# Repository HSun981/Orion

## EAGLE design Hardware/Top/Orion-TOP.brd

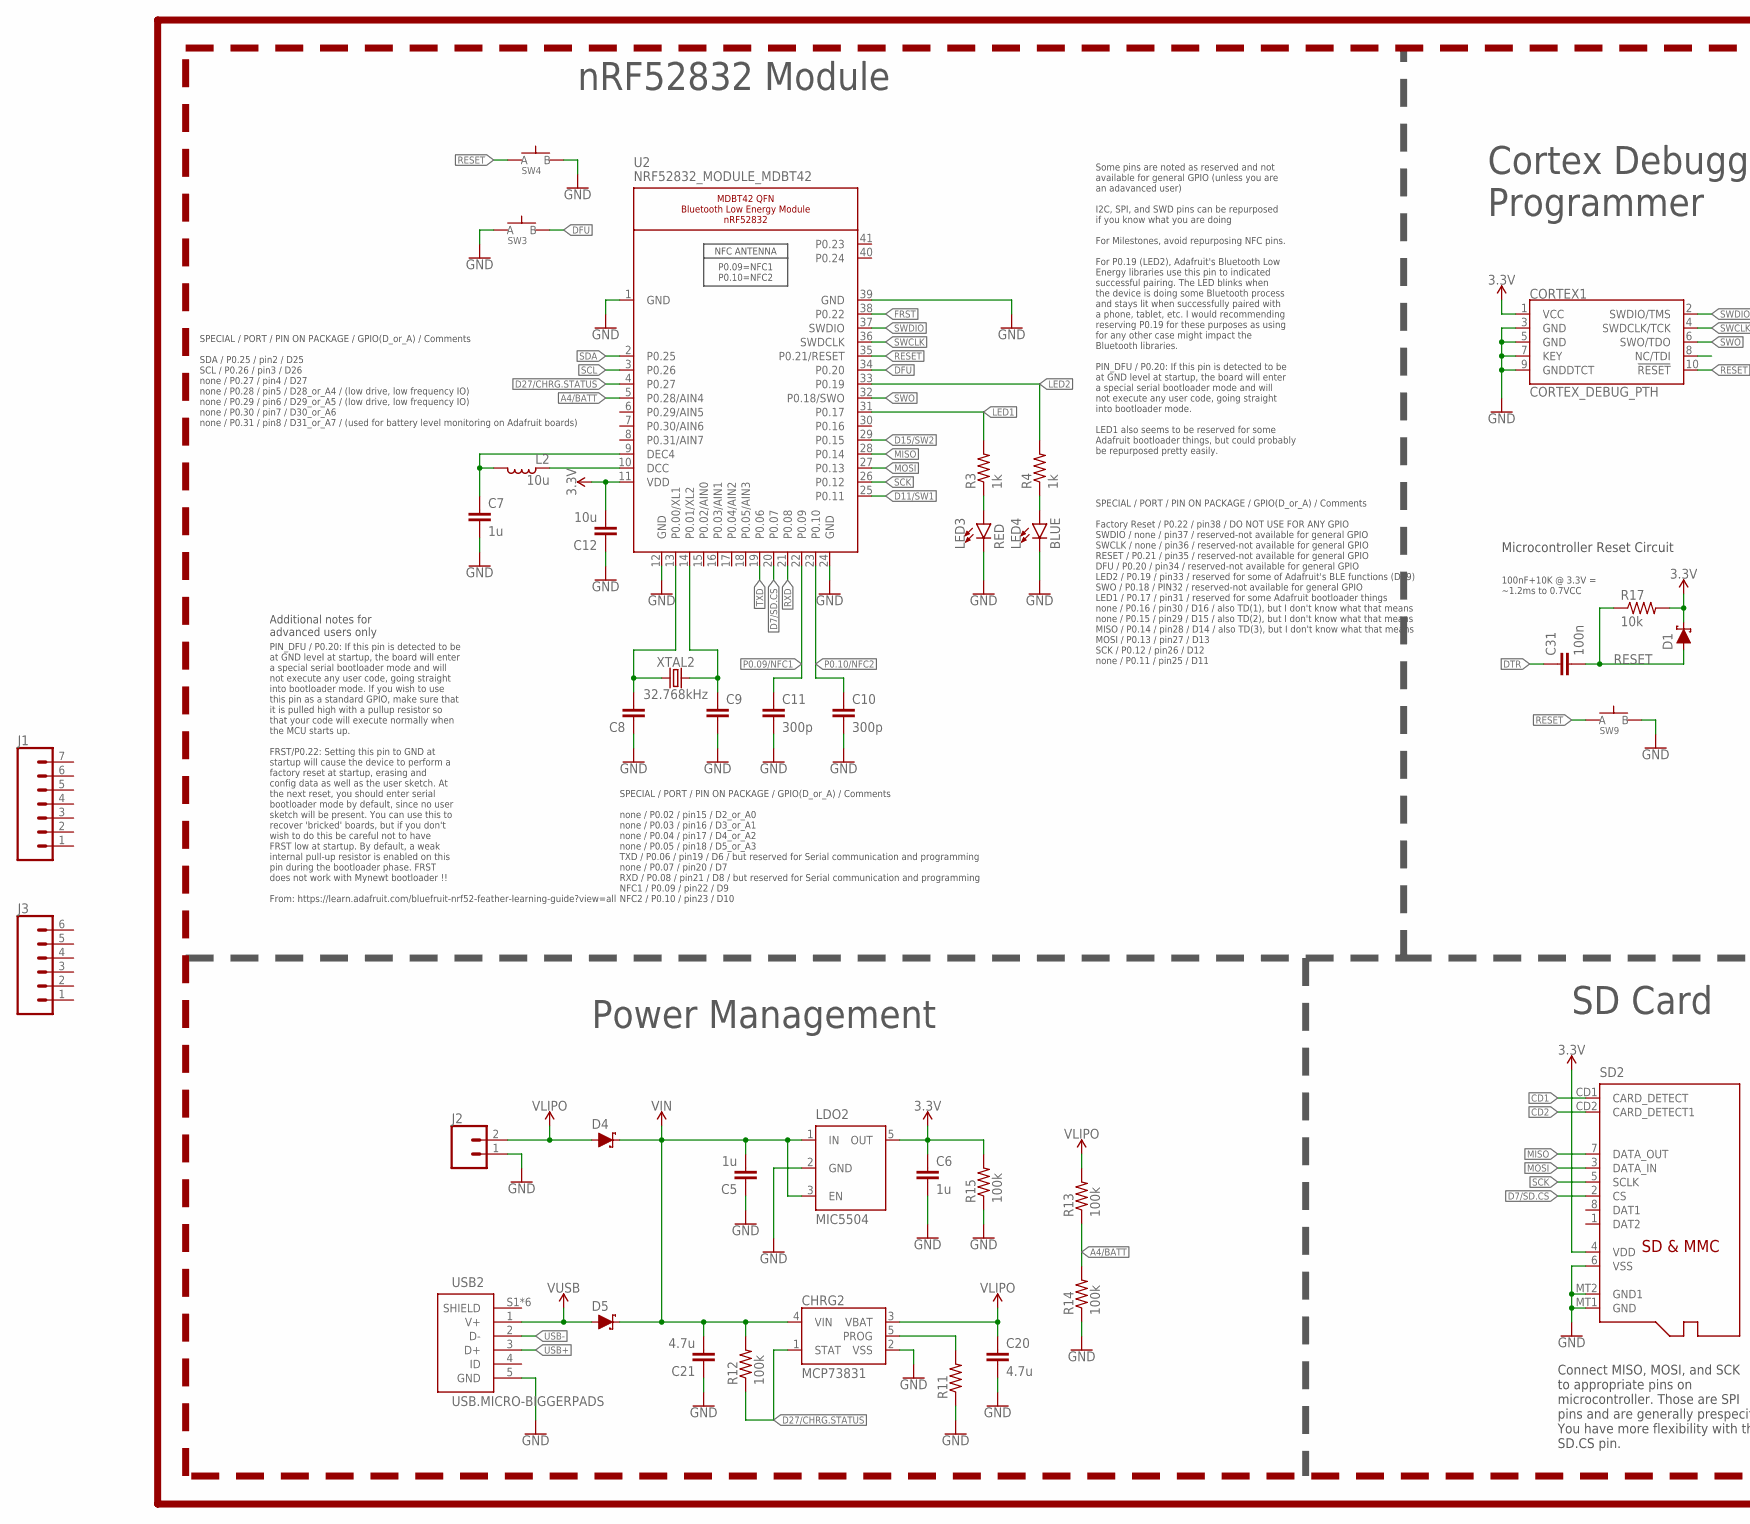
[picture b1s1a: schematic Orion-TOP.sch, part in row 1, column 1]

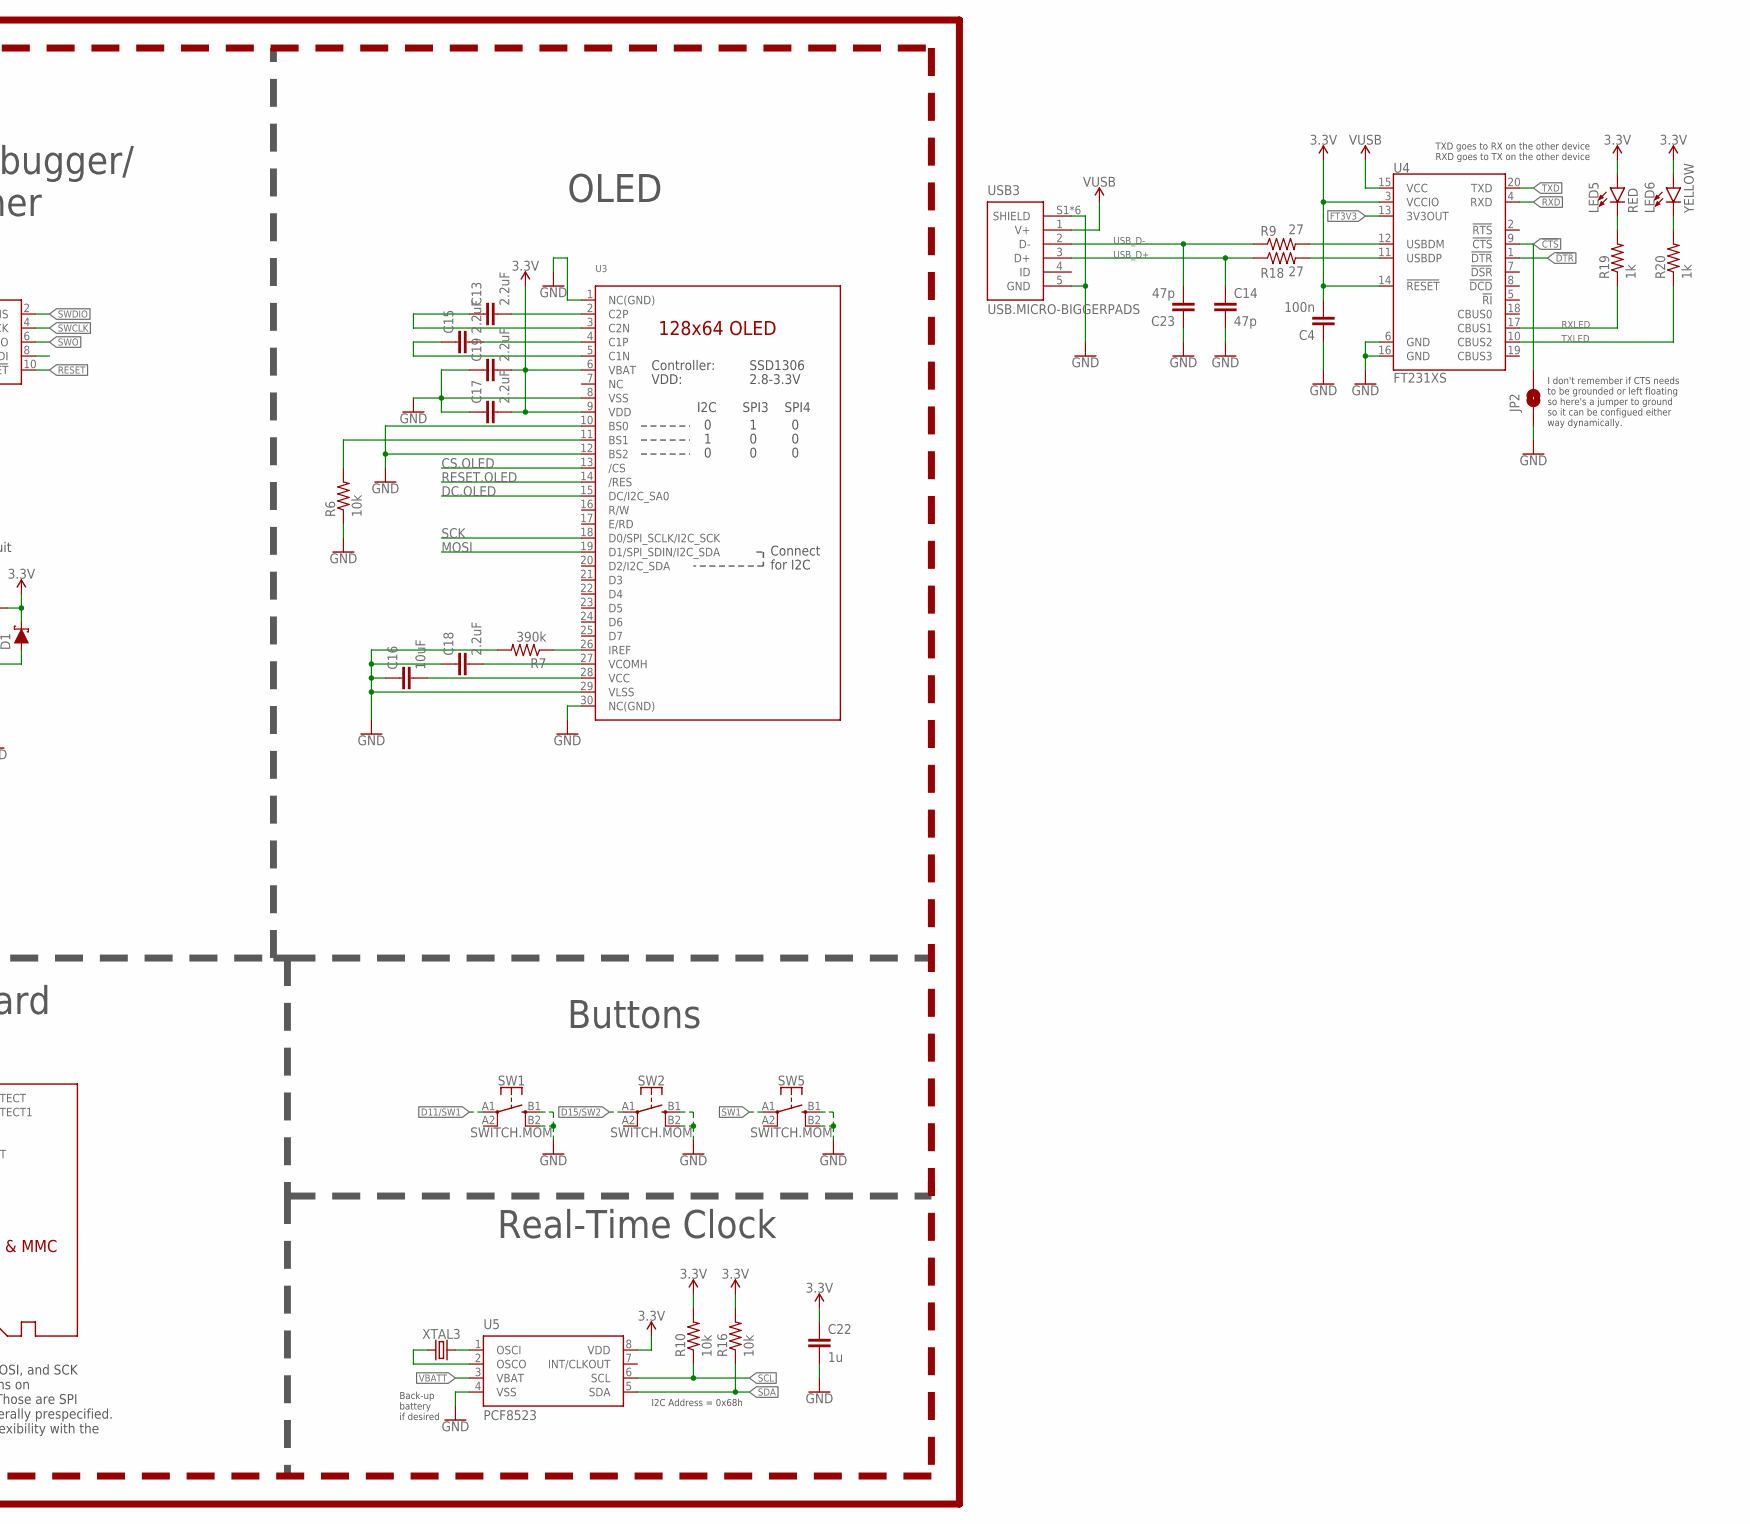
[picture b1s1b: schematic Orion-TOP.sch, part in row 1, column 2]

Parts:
C4, C31: 100n; C0603
C5, C6, C7, C22: 1u; C0603
C8, C9: CAPACITOR0603; C0603
C10, C11: 300p; C0603
C12: 10u; C0805
C13, C15, C17, C18, C19: 2.2uF; C0402
C14, C23: 47p; C0603
C16: 10uF; C0603
C20, C21: 4.7u; C0603
CHRG2: MCP73831; SOT23-5
CORTEX1: CORTEX_DEBUG_PTH; 2X5-PTH-1.27MM
D1, D4, D5: SCHOTTKY-USC; USC
J1: CONN_07; 1X07
J2: CONN_02; 1X02
J3: CONN_061.27MM; 1X06_1.27MM
JP2: JUMPER-SMT_2_NO_SILK; SMT-JUMPER_2_NO_SILK
L2: 10u; L0603
LDO2: MIC5504; SOT23-5
LED3, LED5: RED; LED-0603
LED4: BLUE; LED-0603
LED6: YELLOW; LED-0603
R3, R4, R19, R20: 1k; R0603
R6, R10, R16, R17: 10k; R0603
R7: 390k; R0603
R9, R18: 27; R0603
R11: RESISTOR0603; R0603
R12, R13, R14, R15: 100k; R0603
SD2: MICROSD
SW1, SW2, SW5: SWITCH.MOM; TACTILE_SWITCH_SMD_6.2MM_TALL
SW3, SW4, SW9: SPST-PTS830GG140-COPY.1-3; BUTTON-GULLWING
U2: NRF52832_MODULE_MDBT42; BLE_MODULE_RAYTAC_MDBT42
U3: DISP_OLED_UG-2864HSWEG01-NO-WRAPAROUND; UG-2864HSWEG01_0.96IN_NO-WRAPAROUND
U4: FT231XS; SSOP20_L
U5: PCF8523; SO8; DIGIKEY 568-5306-1-ND
USB2, USB3: USB.MICRO-BIGGERPADS; USB-MICRO-01.BIGGERPADS
XTAL2: 32.768kHz; 2-SMD.NOLEAD.2.0MMTO1.2MM
XTAL3: 32.7680kHz; 2-SMD.NOLEAD.2.0MMTO1.2MM

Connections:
3.3V: C4.2, C6.1, C12.2, C17.2, C19.2, C22.1, CORTEX1.1 (VCC), D1.- (C), LDO2.5 (OUT), LED5.A, LED6.A, R10.2, R15.2, R16.2, R17.2, SD2.4 (VDD), U2.11 (VDD), U3.6 (VBAT), U3.9 (VDD), U4.3 (VCCIO), U4.14 (!RESET), U5.8 (VDD)
!CTS: JP2.2, U4.9 (!CTS)
!DTR: U4.1 (!DTR)
A4/BATT: R13.1, R14.2, U2.5 (P0.28/AIN4)
CD1: SD2.CD1 (CARD_DETECT)
CD2: SD2.CD2 (CARD_DETECT1)
CS.OLED: U3.13 (/CS)
D7/SD.CS: SD2.2 (CS), U2.20 (P0.07)
D11/SW1: SW1.A1 (1), U2.25 (P0.11)
D15/SW2: SW2.A1 (1), U2.29 (P0.15)
D27/CHRG.STATUS: CHRG2.1 (STAT), R12.1, U2.4 (P0.27)
DC.OLED: U3.15 (DC/I2C_SA0)
DFU: SW3.3 (B), U2.34 (P0.20)
DTR: C31.1
FRST: U2.38 (P0.22)
FT3V3: U4.13 (3V3OUT)
GND: C4.1, C5.1, C6.2, C7.2, C8.1, C9.2, C10.2, C11.2, C12.1, C14.2, C16.1, C17.1, C18.1, C19.1, C20.2, C21.1, C22.2, C23.1, CHRG2.2 (VSS), CORTEX1.3 (GND), CORTEX1.5 (GND), CORTEX1.7 (KEY), CORTEX1.9 (GNDDTCT), J2.1, JP2.1, LDO2.2 (GND), LED3.C, LED4.C, R6.1, R7.2, R11.1, R14.1, R15.1, SD2.6 (VSS), SD2.MT1 (GND), SD2.MT2 (GND1), SW1.B1 (3), SW1.B2 (4), SW2.B1 (3), SW2.B2 (4), SW3.1 (A), SW4.3 (B), SW5.B1 (3), SW5.B2 (4), SW9.3 (B), U2.1 (GND), U2.12 (GND), U2.24 (GND), U2.39 (GND), U3.1 (NC(GND)), U3.8 (VSS), U3.10 (BS0), U3.12 (BS2), U3.29 (VLSS), U3.30 (NC(GND)), U4.6 (GND), U4.16 (GND), U5.4 (VSS), USB2.5 (GND), USB3.5 (GND), USB3.S1 (SHIELD), USB3.S2 (SHIELD), USB3.S3 (SHIELD), USB3.S4 (SHIELD), USB3.S5 (SHIELD), USB3.S6 (SHIELD)
LED1: R3.2, U2.31 (P0.17)
LED2: R4.2, U2.33 (P0.19)
MISO: SD2.7 (DATA_OUT), U2.28 (P0.14)
MOSI: SD2.3 (DATA_IN), U2.27 (P0.13), U3.19 (D1/SPI_SDIN/I2C_SDA)
unnamed: R6.2, U3.11 (BS1)
unnamed: R7.1, U3.26 (IREF)
unnamed: C13.2, U3.2 (C2P)
unnamed: C8.2, U2.13 (P0.00/XL1), XTAL2.P$1 (1)
unnamed: C13.1, U3.3 (C2N)
unnamed: C9.1, U2.14 (P0.01/XL2), XTAL2.P$2 (2)
unnamed: C15.2, U3.4 (C1P)
unnamed: C15.1, U3.5 (C1N)
unnamed: LED3.A, R3.1
unnamed: LED4.A, R4.1
unnamed: L2.1, U2.10 (DCC)
unnamed: C7.1, L2.2, U2.9 (DEC4)
unnamed: C16.2, U3.28 (VCC)
unnamed: C18.2, U3.27 (VCOMH)
unnamed: CHRG2.5 (PROG), R11.2
unnamed: U5.2 (OSCO), XTAL3.P$1 (1)
unnamed: U5.1 (OSCI), XTAL3.P$2 (2)
unnamed: R9.2, U4.12 (USBDM)
unnamed: R18.2, U4.11 (USBDP)
unnamed: LED5.C, R19.2
unnamed: LED6.C, R20.2
P0.09/NFC1: C11.1, U2.22 (P0.09)
P0.10/NFC2: C10.1, U2.23 (P0.10)
RESET: C31.2, CORTEX1.10 (!RESET), D1.+ (A), R17.1, SW4.1 (A), SW9.1 (A), U2.35 (P0.21/RESET)
RESET.OLED: U3.14 (/RES)
RXD: U2.21 (P0.08), U4.4 (RXD)
RXLED: R19.1, U4.17 (CBUS1)
SCK: SD2.5 (SCLK), U2.26 (P0.12), U3.18 (D0/SPI_SCLK/I2C_SCK)
SCL: R10.1, U2.3 (P0.26), U5.6 (SCL)
SDA: R16.1, U2.2 (P0.25), U5.5 (SDA)
SW1: SW5.A1 (1)
SWCLK: CORTEX1.4 (SWDCLK/TCK), U2.36 (SWDCLK)
SWDIO: CORTEX1.2 (SWDIO/TMS), U2.37 (SWDIO)
SWO: CORTEX1.6 (SWO/TDO), U2.32 (P0.18/SWO)
TXD: U2.19 (P0.06), U4.20 (TXD)
TXLED: R20.1, U4.10 (CBUS2)
USB+: USB2.3 (D+)
USB-: USB2.2 (D-)
USB_D+: C14.1, R18.1, USB3.3 (D+)
USB_D-: C23.2, R9.1, USB3.2 (D-)
VBATT: U5.3 (VBAT)
VIN: C5.2, C21.2, CHRG2.4 (VIN), D4.- (C), D5.- (C), LDO2.1 (IN), LDO2.3 (EN), R12.2
VLIPO: C20.1, CHRG2.3 (VBAT), D4.+ (A), J2.2, R13.2
V_USB: D5.+ (A), U4.15 (VCC), USB2.1 (V+), USB3.1 (V+)

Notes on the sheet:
SPECIAL / PORT / PIN ON PACKAGE / GPIO(D_or_A) / Comments SDA / P0.25 / pin2 / D25 SCL / P0.26 / pin3 / D26 none / P0.27 / pin4 / D27 none / P0.28 / pin5 / D28_or_A4 / (low drive, low frequency IO) none / P0.29 / pin6 / D29_or_A5 / (low drive, low frequency IO) none / P0.30 / pin7 / D30_or_A6 none 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
SPECIAL / PORT / PIN ON PACKAGE / GPIO(D_or_A) / Comments none / P0.02 / pin15 / D2_or_A0 none / P0.03 / pin16 / D3_or_A1 none / P0.04 / pin17 / D4_or_A2 none / P0.05 / pin18 / D5_or_A3 TXD / P0.06 / pin19 / D6 / but reserved for Serial communication and programming none / P0.07 / pin20 / D7 RXD / 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
SPECIAL / PORT / PIN ON PACKAGE / GPIO(D_or_A) / Comments Factory Reset / P0.22 / pin38 / DO NOT USE FOR ANY GPIO SWDIO / none / pin37 / reserved-not available for general GPIO SWCLK / none / pin36 / reserved-not available for general GPIO RESET / P0.21 / pin35 / reserved-not available for general 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
Some pins are noted as reserved and not available for general GPIO (unless you are an adavanced user) I2C, SPI, and SWD pins can be repurposed if you know what you are doing For Milestones, avoid repurposing NFC pins. For P0.19 (LED2), Adafruit's Bluetooth Low Energy libraries use this pin to indic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
PIN_DFU / P0.20: If this pin is detected to be at GND level at startup, the board will enter a special serial bootloader mode and will not execute any user code, going straight into bootloader mode. If you wish to use this pin as a standard GPIO, make sure that it is pulled high with a pullup resis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
Additional notes for advanced users only
Connect MISO, MOSI, and SCK to appropriate pins on microcontroller. Those are SPI pins and are generally prespecified. You have more flexibility with the SD.CS pin.
I2C Address = 0x68h
Back-up battery if desired
nRF52832 Module
Cortex Debugger/ Programmer
OLED
Power Management
SD Card
Buttons
Real-Time Clock
Microcontroller Reset Circuit
100nF+10K @ 3.3V = ~1.2ms to 0.7VCC
TXD goes to RX on the other device RXD goes to TX on the other device
I don't remember if CTS needs to be grounded or left floating so here's a jumper to ground so it can be configued either way dynamically.

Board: 2 copper layers, 67 parts (2 on the bottom side), 52 nets, no tracks yet.

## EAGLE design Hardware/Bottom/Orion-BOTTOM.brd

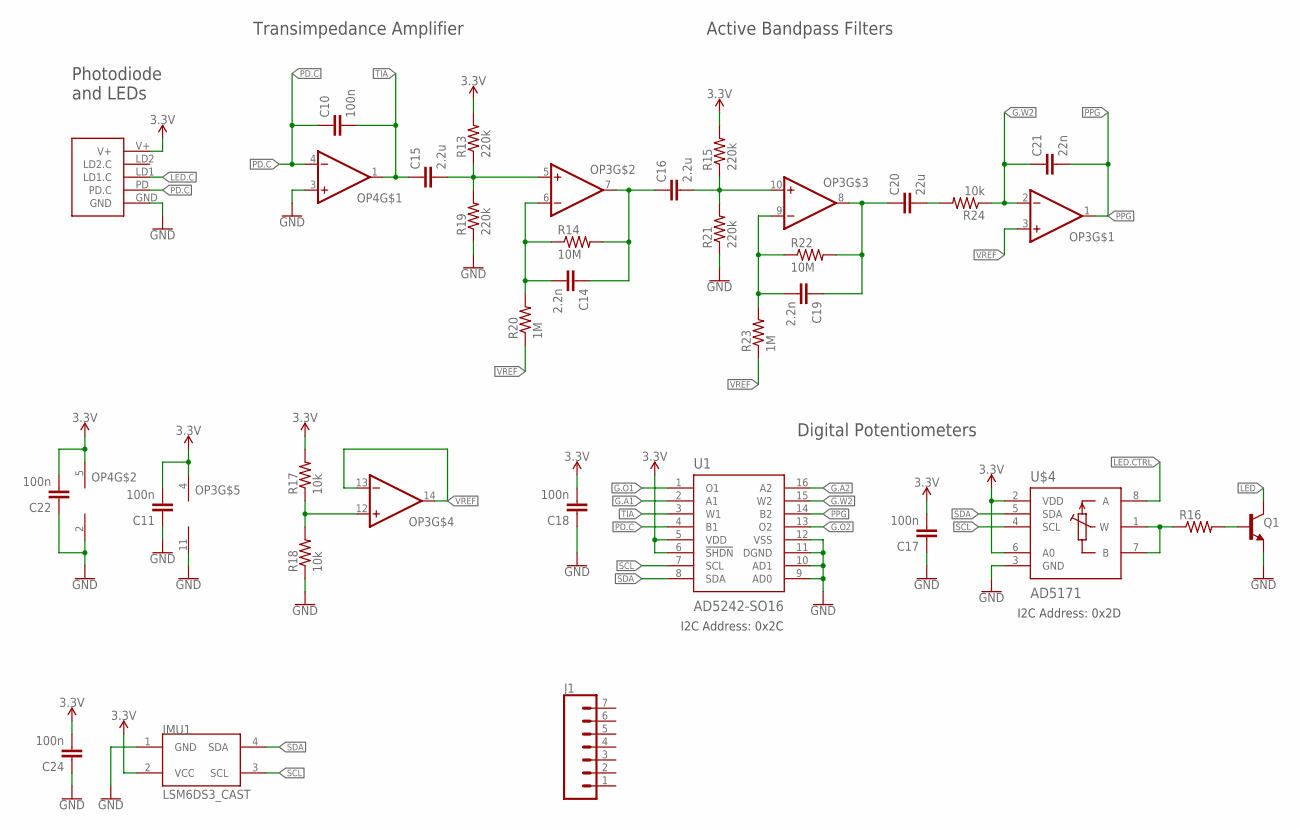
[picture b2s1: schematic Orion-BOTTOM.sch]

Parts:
C10, C11, C17, C18, C22, C24: 100n; C0603
C14, C19: 2.2n; C0603
C15, C16: 2.2u; C0603
C20: 22u; C0603
C21: 22n; C0603
IMU1: LSM6DS3_CAST
J1: CONN_07; 1X07
OP3: OP-QUAD-SO14; SO14
OP4: OP-SINGLEOT; SOT23-5
Q1: NPN-GENERIC; SOT23-3
R13, R15, R19, R21: 220k; R0603
R14, R22: 10M; R0603
R16: RESISTOR0603; R0603
R17, R18: 10k; R0402
R20, R23: 1M; R0603
R24: 10k; R0603
U1: AD5242-SO16; SO16
U$3: PPG.MODULE.2
U$4: AD5171; SOT-23-8

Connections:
3.3V: C11.2, C17.2, C18.2, C22.2, C24.2, IMU1.2 (VCC), OP3.4 (V+), OP4.5 (V+), R13.2, R15.2, R17.2, U1.5 (VDD), U1.6 (!SHDN), U$3.V+, U$4.2 (VDD), U$4.6 (A0)
G.A1: U1.2 (A1)
G.A2: U1.16 (A2)
G.O1: U1.1 (O1)
G.O2: U1.13 (O2)
G.W2: C21.1, OP3.2 (-IN), R24.1, U1.15 (W2)
GND: C11.1, C17.1, C18.1, C22.1, C24.1, IMU1.1 (GND), OP3.11 (V-), OP4.2 (V-), OP4.3 (+IN), Q1.2 (E), R18.1, R19.1, R21.1, U1.9 (AD0), U1.10 (AD1), U1.11 (DGND), U1.12 (VSS), U$3.GND, U$4.3 (GND)
LED: Q1.3 (C)
LED.C: U$3.LD1 (LD1.C)
LED.CTRL: U$4.8 (A)
unnamed: Q1.1 (B), R16.2
unnamed: R16.1, U$4.1 (W), U$4.7 (B)
unnamed: OP3.12 (+IN), R17.1, R18.2
unnamed: C15.2, OP3.5 (+IN), R13.1, R19.2
unnamed: C14.2, OP3.6 (-IN), R14.1, R20.2
unnamed: C14.1, C16.1, OP3.7 (OUT), R14.2
unnamed: C16.2, OP3.10 (+IN), R15.1, R21.2
unnamed: C19.2, OP3.9 (-IN), R22.1, R23.2
unnamed: C19.1, C20.1, OP3.8 (OUT), R22.2
unnamed: C20.2, R24.2
PD.C: C10.1, OP4.4 (-IN), U1.4 (B1), U$3.PD (PD.C)
PPG: C21.2, OP3.1 (OUT), U1.14 (B2)
SCL: IMU1.3 (SCL), U1.7 (SCL), U$4.4 (SCL)
SDA: IMU1.4 (SDA), U1.8 (SDA), U$4.5 (SDA)
TIA: C10.2, C15.1, OP4.1 (OUT), U1.3 (W1)
VREF: OP3.3 (+IN), OP3.13 (-IN), OP3.14 (OUT), R20.1, R23.1

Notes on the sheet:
Photodiode and LEDs
Active Bandpass Filters
Digital Potentiometers
Transimpedance Amplifier
I2C Address: 0x2C
I2C Address: 0x2D

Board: 2 copper layers, 32 parts (0 on the bottom side), 19 nets, no tracks yet.

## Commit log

2020-05-28 Add files via upload
    list of the device's features
2020-06-04 add firmware
2020-06-04 Rename
2020-06-05 add Hardware
2020-06-05 modified the top layer of hardware
2020-06-11 modified top board schemetics: add buttons and organized
2020-06-25 remove temp storage files
2020-06-25 add the Power class
2020-06-25 fixed a bug and it compiles now
2020-07-02 fixed some missing design blocks
